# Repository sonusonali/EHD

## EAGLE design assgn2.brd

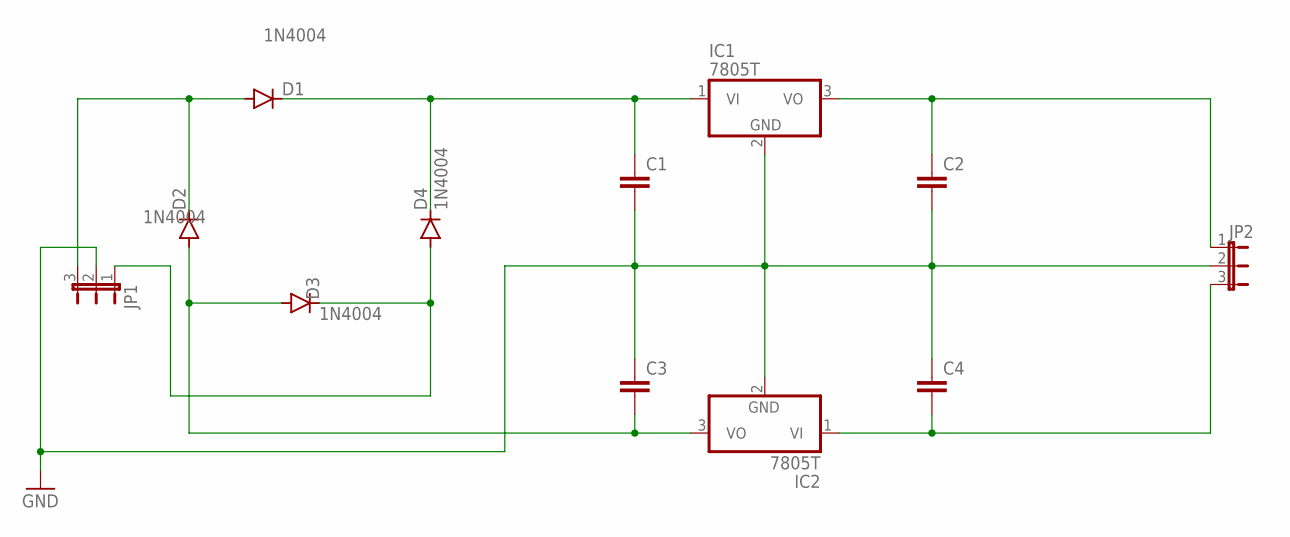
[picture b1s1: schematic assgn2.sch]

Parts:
C1, C2, C3, C4: C2,5-3; C2.5-3
D1, D2, D3, D4: 1N4004; DO41-10
IC1, IC2: 7805T; TO220H
JP1, JP2: JP2E; JP2

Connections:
GND: C1.2, C2.2, C3.1, C4.1, IC1.2 (GND), IC2.2 (GND), JP1.2, JP2.2
unnamed: D1.A, D2.C, JP1.3
unnamed: C4.2, IC2.1 (VI), JP2.3
unnamed: C2.1, IC1.3 (VO), JP2.1
unnamed: C1.1, D1.C, D4.C, IC1.1 (VI)
unnamed: D3.C, D4.A, JP1.1
unnamed: C3.2, D2.A, D3.A, IC2.3 (VO)

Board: 2 copper layers, 12 parts (0 on the bottom side), 7 nets, no tracks yet.

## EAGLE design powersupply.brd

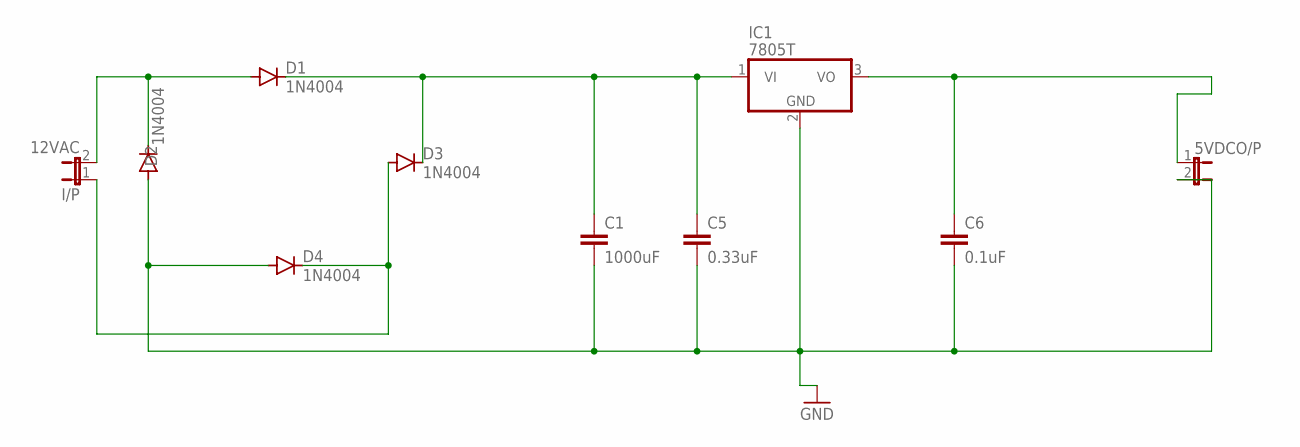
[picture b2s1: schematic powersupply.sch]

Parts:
5VDCO/P: JP1E; JP1
C1: 1000uF; C2.5-3
C5: 0.33uF; C2.5-3
C6: 0.1uF; C2.5-3
D1, D2, D3, D4: 1N4004; DO41-10
I/P: 12VAC; JP1
IC1: 7805T; TO220H

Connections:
unnamed: D1.A, D2.C, I/P.2
unnamed: C1.1, C5.1, D1.C, D3.C, IC1.1 (VI)
unnamed: D3.A, D4.C, I/P.1
unnamed: 5VDCO/P.2, C1.2, C5.2, C6.2, D2.A, D4.A, IC1.2 (GND)
unnamed: 5VDCO/P.1, C6.1, IC1.3 (VO)

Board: 2 copper layers, 10 parts (0 on the bottom side), 5 nets, no tracks yet.
